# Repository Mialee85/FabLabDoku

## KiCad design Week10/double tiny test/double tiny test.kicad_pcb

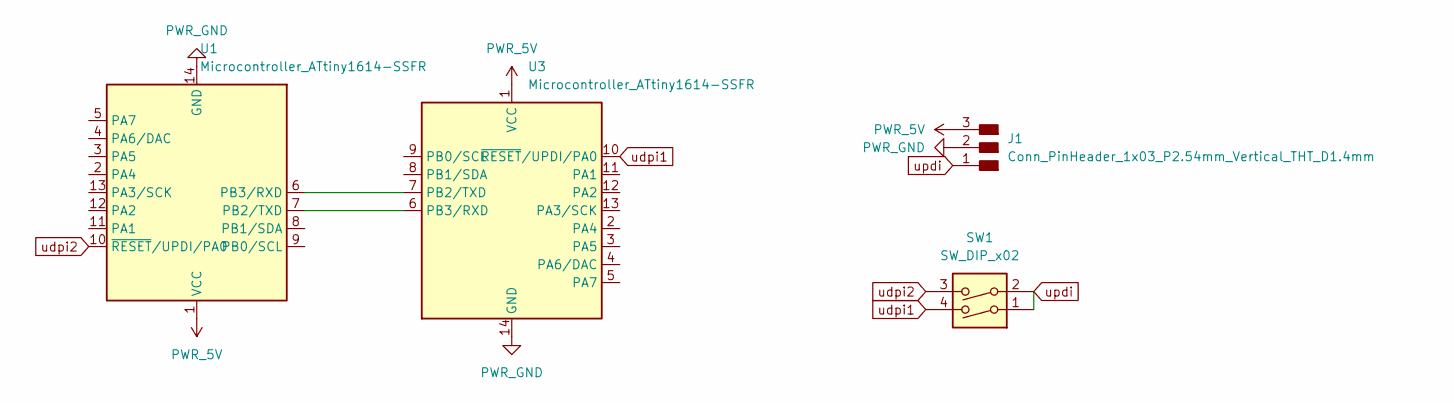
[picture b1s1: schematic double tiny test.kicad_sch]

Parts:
J1: Conn_PinHeader_1x03_P2.54mm_Vertical_THT_D1.4mm; PinHeader_1x03_P2.54mm_Vertical_THT_D1.4mm
SW1: SW_DIP_x02; SW_DIP_SPSTx02_Slide_9.78x7.26mm_W8.61mm_P2.54mm
U1, U3: Microcontroller_ATtiny1614-SSFR; SOIC-14_3.9x8.7mm_P1.27mm

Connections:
unnamed: U1.7 (PB2/TXD), U3.6 (PB3/RXD)
unnamed: U1.6 (PB3/RXD), U3.7 (PB2/TXD)
PWR_5V: J1.3, U1.1 (VCC), U3.1 (VCC)
PWR_GND: J1.2, U1.14 (GND), U3.14 (GND)
udpi1: SW1.4, U3.10 (~RESET/UPDI/PA0)
udpi2: SW1.3, U1.10 (~RESET/UPDI/PA0)
updi: J1.1, SW1.1, SW1.2

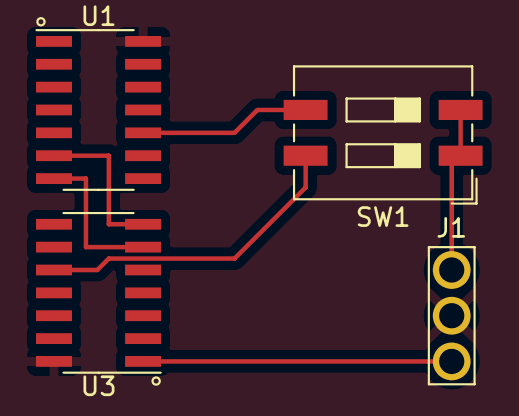
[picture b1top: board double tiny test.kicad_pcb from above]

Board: 2 copper layers, 4 parts (0 on the bottom side), 7 nets.

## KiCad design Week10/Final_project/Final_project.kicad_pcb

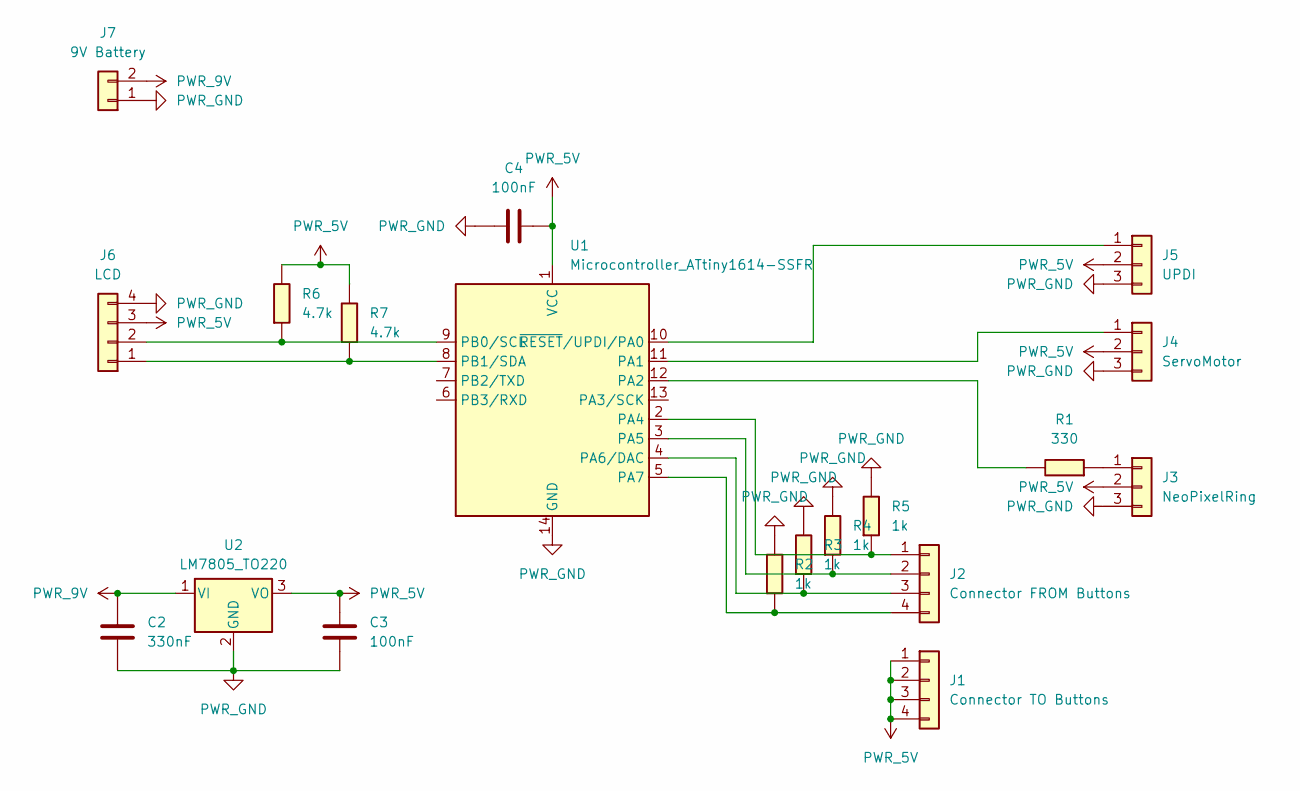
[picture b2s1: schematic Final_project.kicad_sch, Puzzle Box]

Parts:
C2: 330nF; C_1206
C3, C4: 100nF; C_1206
J1: Connector TO Buttons; JST_XH_B4B-XH-A_1x04_P2.50mm_Vertical
J2: Connector FROM Buttons; JST_XH_B4B-XH-A_1x04_P2.50mm_Vertical
J3: NeoPixelRing; JST_XH_B3B-XH-A_1x03_P2.50mm_Vertical
J4: ServoMotor; JST_XH_B3B-XH-A_1x03_P2.50mm_Vertical
J5: UPDI; JST_XH_B3B-XH-A_1x03_P2.50mm_Vertical
J6: LCD; JST_XH_B4B-XH-A_1x04_P2.50mm_Vertical
J7: 9V Battery; JST_XH_B2B-XH-A_1x02_P2.50mm_Vertical
R1: 330; R_1206
R2, R3, R4, R5: 1k; R_1206
R6, R7: 4.7k; R_1206
U1: Microcontroller_ATtiny1614-SSFR; SOIC-14_3.9x8.7mm_P1.27mm
U2: LM7805_TO220; TO-220-3_Vertical

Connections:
unnamed: J2.1, R5.2, U1.2 (PA4)
unnamed: J2.2, R4.2, U1.3 (PA5)
unnamed: J2.3, R3.2, U1.4 (PA6/DAC)
unnamed: J2.4, R2.2, U1.5 (PA7)
unnamed: J3.1, R1.2
unnamed: J4.1, U1.11 (PA1)
unnamed: J5.1, U1.10 (~RESET/UPDI/PA0)
unnamed: J6.1, R7.2, U1.8 (PB1/SDA)
unnamed: J6.2, R6.2, U1.9 (PB0/SCL)
unnamed: R1.1, U1.12 (PA2)
PWR_5V: C3.1, C4.2, J1.1, J1.2, J1.3, J1.4, J3.2, J4.2, J5.2, J6.3, R6.1, R7.1, U1.1 (VCC), U2.3 (VO)
PWR_9V: C2.1, J7.2, U2.1 (VI)
PWR_GND: C2.2, C3.2, C4.1, J3.3, J4.3, J5.3, J6.4, J7.1, R2.1, R3.1, R4.1, R5.1, U1.14 (GND), U2.2 (GND)

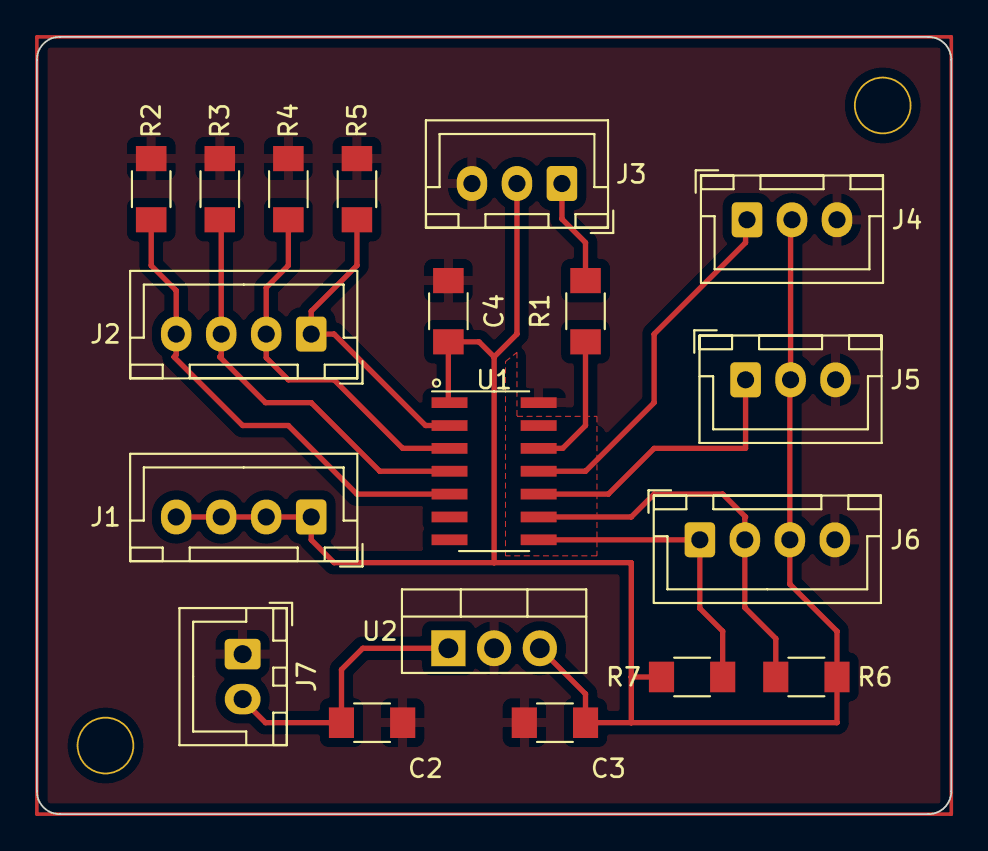
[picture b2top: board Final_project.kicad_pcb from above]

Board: 2 copper layers, 50.8 x 43.2 mm, 19 parts (0 on the bottom side), 13 nets.

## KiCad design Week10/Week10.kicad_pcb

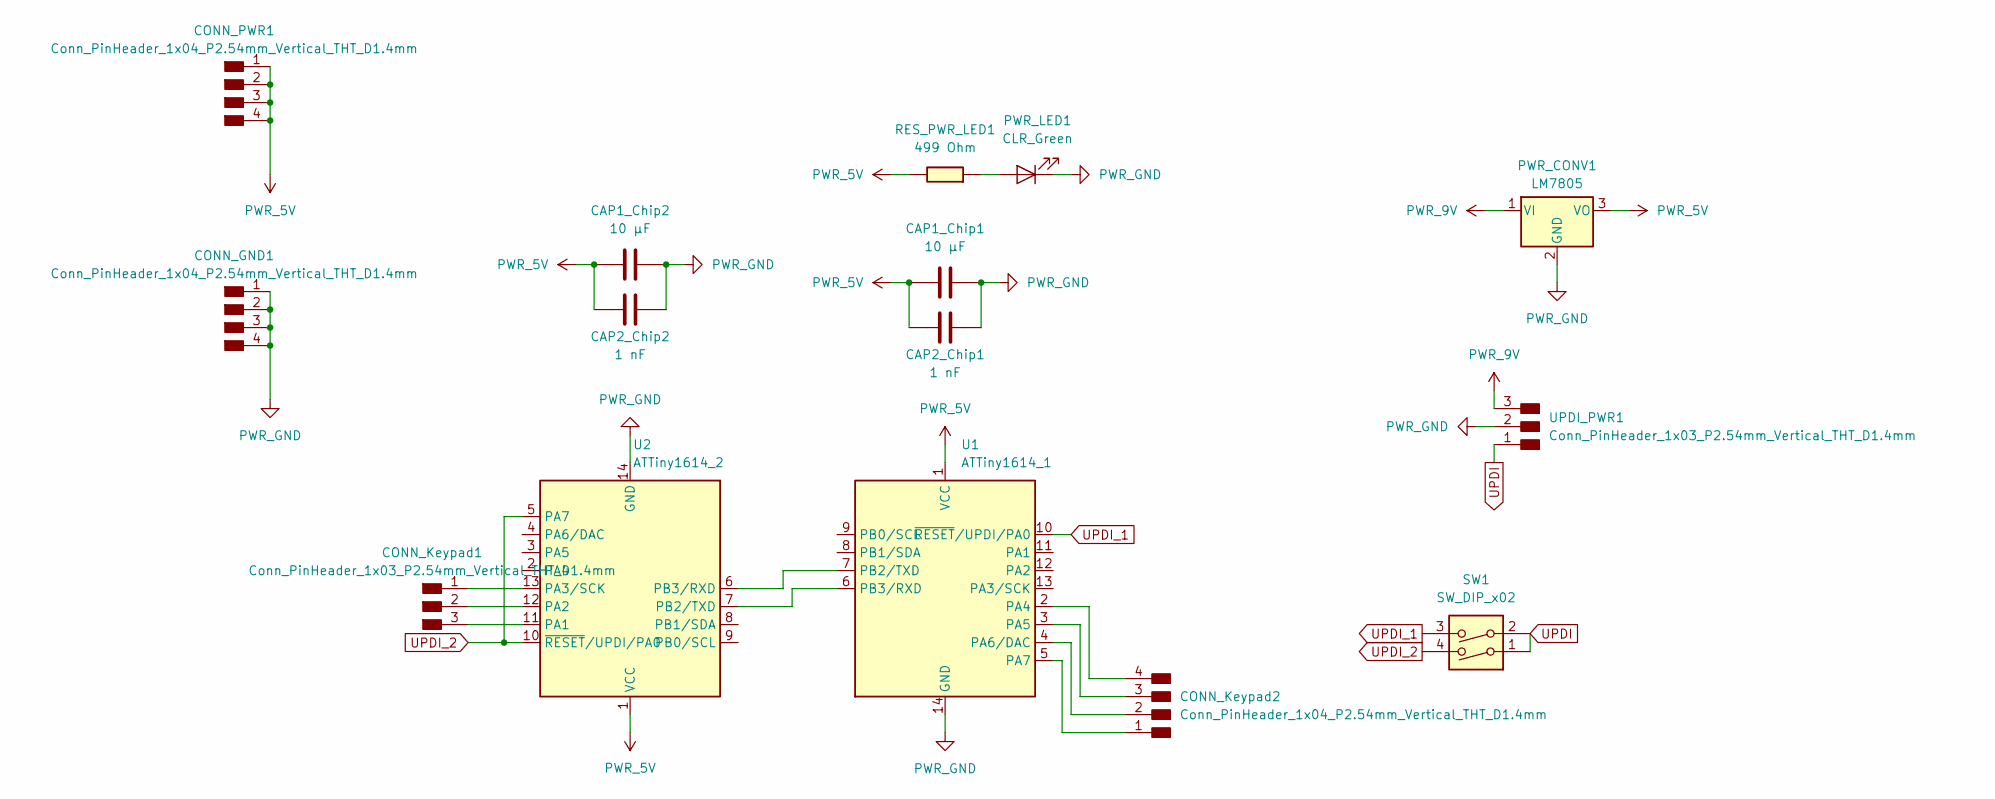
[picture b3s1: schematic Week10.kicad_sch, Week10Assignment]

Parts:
CAP1_Chip1, CAP1_Chip2: 10 µF; C_1206
CAP2_Chip1, CAP2_Chip2: 1 nF; C_1206
CONN_GND1: Conn_PinHeader_1x04_P2.54mm_Vertical_THT_D1.4mm; PinHeader_1x04_P2.54mm_Vertical_THT_D1.4mm
CONN_Keypad1: Conn_PinHeader_1x03_P2.54mm_Vertical_THT_D1.4mm; PinHeader_1x03_P2.54mm_Vertical_THT_D1.4mm
CONN_Keypad2: Conn_PinHeader_1x04_P2.54mm_Vertical_THT_D1.4mm; PinHeader_1x04_P2.54mm_Vertical_THT_D1.4mm
CONN_PWR1: Conn_PinHeader_1x04_P2.54mm_Vertical_THT_D1.4mm; PinHeader_1x04_P2.54mm_Vertical_THT_D1.4mm
PWR_CONV1: LM7805; TO-220-3_Vertical
PWR_LED1: CLR_Green; LED_1206
RES_PWR_LED1: 499 Ohm; R_1206
SW1: SW_DIP_x02; DIP-4_W7.62mm
U1: ATTiny1614_1; SOIC-14_3.9x8.7mm_P1.27mm
U2: ATTiny1614_2; SOIC-14_3.9x8.7mm_P1.27mm
UPDI_PWR1: Conn_PinHeader_1x03_P2.54mm_Vertical_THT_D1.4mm; PinHeader_1x03_P2.54mm_Vertical_THT_D1.4mm

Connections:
unnamed: CONN_Keypad1.1, U2.13 (PA3/SCK)
unnamed: CONN_Keypad1.2, U2.12 (PA2)
unnamed: CONN_Keypad1.3, U2.11 (PA1)
unnamed: CONN_Keypad2.1, U1.5 (PA7)
unnamed: CONN_Keypad2.2, U1.4 (PA6/DAC)
unnamed: CONN_Keypad2.3, U1.3 (PA5)
unnamed: CONN_Keypad2.4, U1.2 (PA4)
unnamed: PWR_LED1.2 (A), RES_PWR_LED1.2
unnamed: U1.7 (PB2/TXD), U2.6 (PB3/RXD)
unnamed: U1.6 (PB3/RXD), U2.7 (PB2/TXD)
PWR_5V: CAP1_Chip1.1, CAP1_Chip2.1, CAP2_Chip1.1, CAP2_Chip2.1, CONN_PWR1.1, CONN_PWR1.2, CONN_PWR1.3, CONN_PWR1.4, PWR_CONV1.3 (VO), RES_PWR_LED1.1, U1.1 (VCC), U2.1 (VCC)
PWR_9V: PWR_CONV1.1 (VI), UPDI_PWR1.3
PWR_GND: CAP1_Chip1.2, CAP1_Chip2.2, CAP2_Chip1.2, CAP2_Chip2.2, CONN_GND1.1, CONN_GND1.2, CONN_GND1.3, CONN_GND1.4, PWR_CONV1.2 (GND), PWR_LED1.1 (K), U1.14 (GND), U2.14 (GND), UPDI_PWR1.2
UPDI: SW1.1, SW1.2, UPDI_PWR1.1
UPDI_1: SW1.3, U1.10 (~RESET/UPDI/PA0)
UPDI_2: SW1.4, U2.5 (PA7), U2.10 (~RESET/UPDI/PA0)

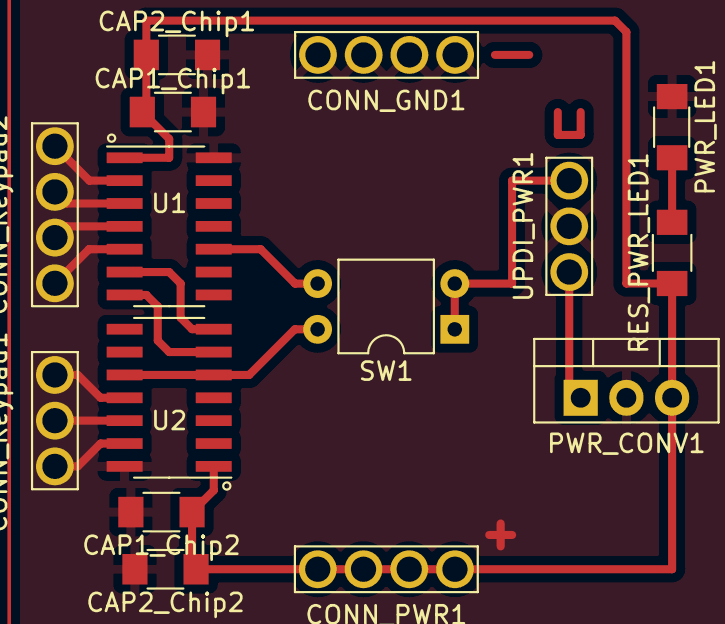
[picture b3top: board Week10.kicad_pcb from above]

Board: 2 copper layers, 15 parts (0 on the bottom side), 16 nets.

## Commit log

2023-12-04 new files
2024-02-06 Upload project
2024-02-06 change dir
2024-02-08 Programmcode upload
2024-02-09 Update 090224
2024-02-16 ATTiny version of program
2024-02-17 Arduino
2024-02-17 Arduino - Serial debug entfernt
2024-02-17 del json
2024-02-17 Ordnerstruktur
2024-02-17 Ordnerstruktur2
2024-02-18 3d printing files
2024-02-18 Files for week 3 and 4
2024-02-19 Biene
2024-02-20 Biene body
2024-02-20 rm empty folder
2024-02-20 week7_8
2024-02-20 adding week 8 files
2024-02-20 Moving folders
2024-02-20 more moving folders and files
2024-02-20 box code
2024-02-20 video
2024-02-20 Poster
2024-02-20 Poster klein
2024-02-20 rename files
2024-04-08 Add wire.h
